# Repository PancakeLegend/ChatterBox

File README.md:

# ChatterBox
Mechanical design for the CCHS ChatterBox project

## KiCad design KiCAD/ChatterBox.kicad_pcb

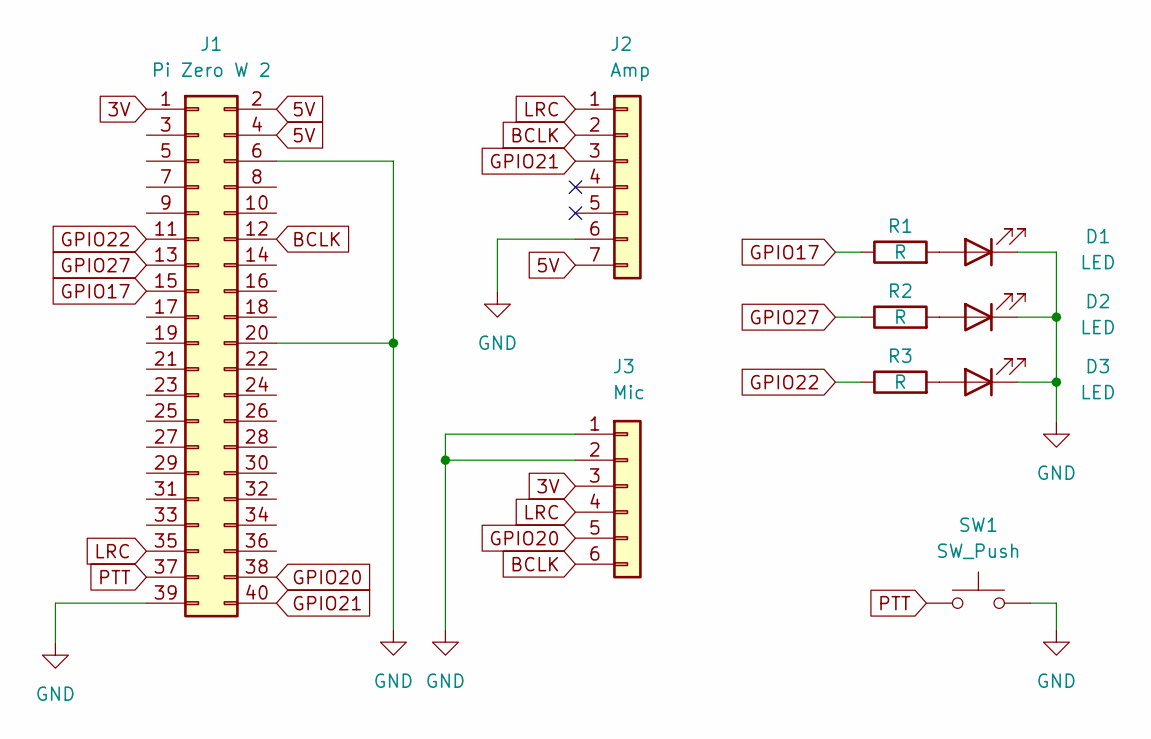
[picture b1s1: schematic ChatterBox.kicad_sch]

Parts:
D1, D2, D3: LED; LED_D5.0mm
J1: Pi Zero W 2
J2: Amp; Amp - MAX98357A
J3: Mic; Mic - INMP441 MEMS I2S
R1, R2, R3: R; R_L6.3mm_D2.5mm_P7.62mm
SW1: SW_Push; Kailh Choc V2 - Arcade Button

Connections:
3V: J1.1, J3.3
5V: J1.2, J1.4, J2.7
BCLK: J1.12, J2.2, J3.6
GND: D1.1 (K), D2.1 (K), D3.1 (K), J1.6, J1.20, J1.39, J2.6, J3.1, J3.2, SW1.2
GPIO17: J1.15, R1.1
GPIO20: J1.38, J3.5
GPIO21: J1.40, J2.3
GPIO22: J1.11, R3.1
GPIO27: J1.13, R2.1
LRC: J1.35, J2.1, J3.4
unnamed: D1.2 (A), R1.2
unnamed: D2.2 (A), R2.2
unnamed: D3.2 (A), R3.2
PTT: J1.37, SW1.1

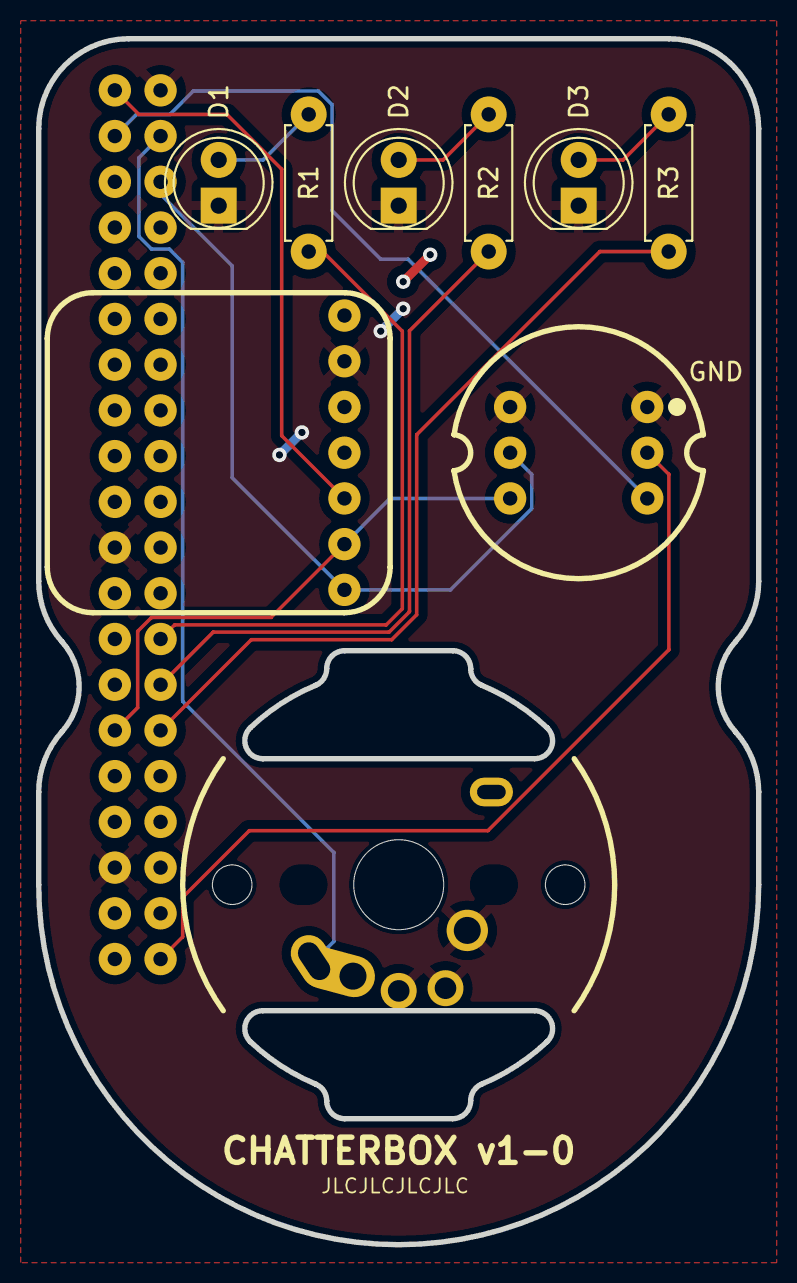
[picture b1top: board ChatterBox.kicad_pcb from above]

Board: 2 copper layers, 40.0 x 67.0 mm, 10 parts (0 on the bottom side), 14 nets.

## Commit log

2025-05-16 modified top plate and case
